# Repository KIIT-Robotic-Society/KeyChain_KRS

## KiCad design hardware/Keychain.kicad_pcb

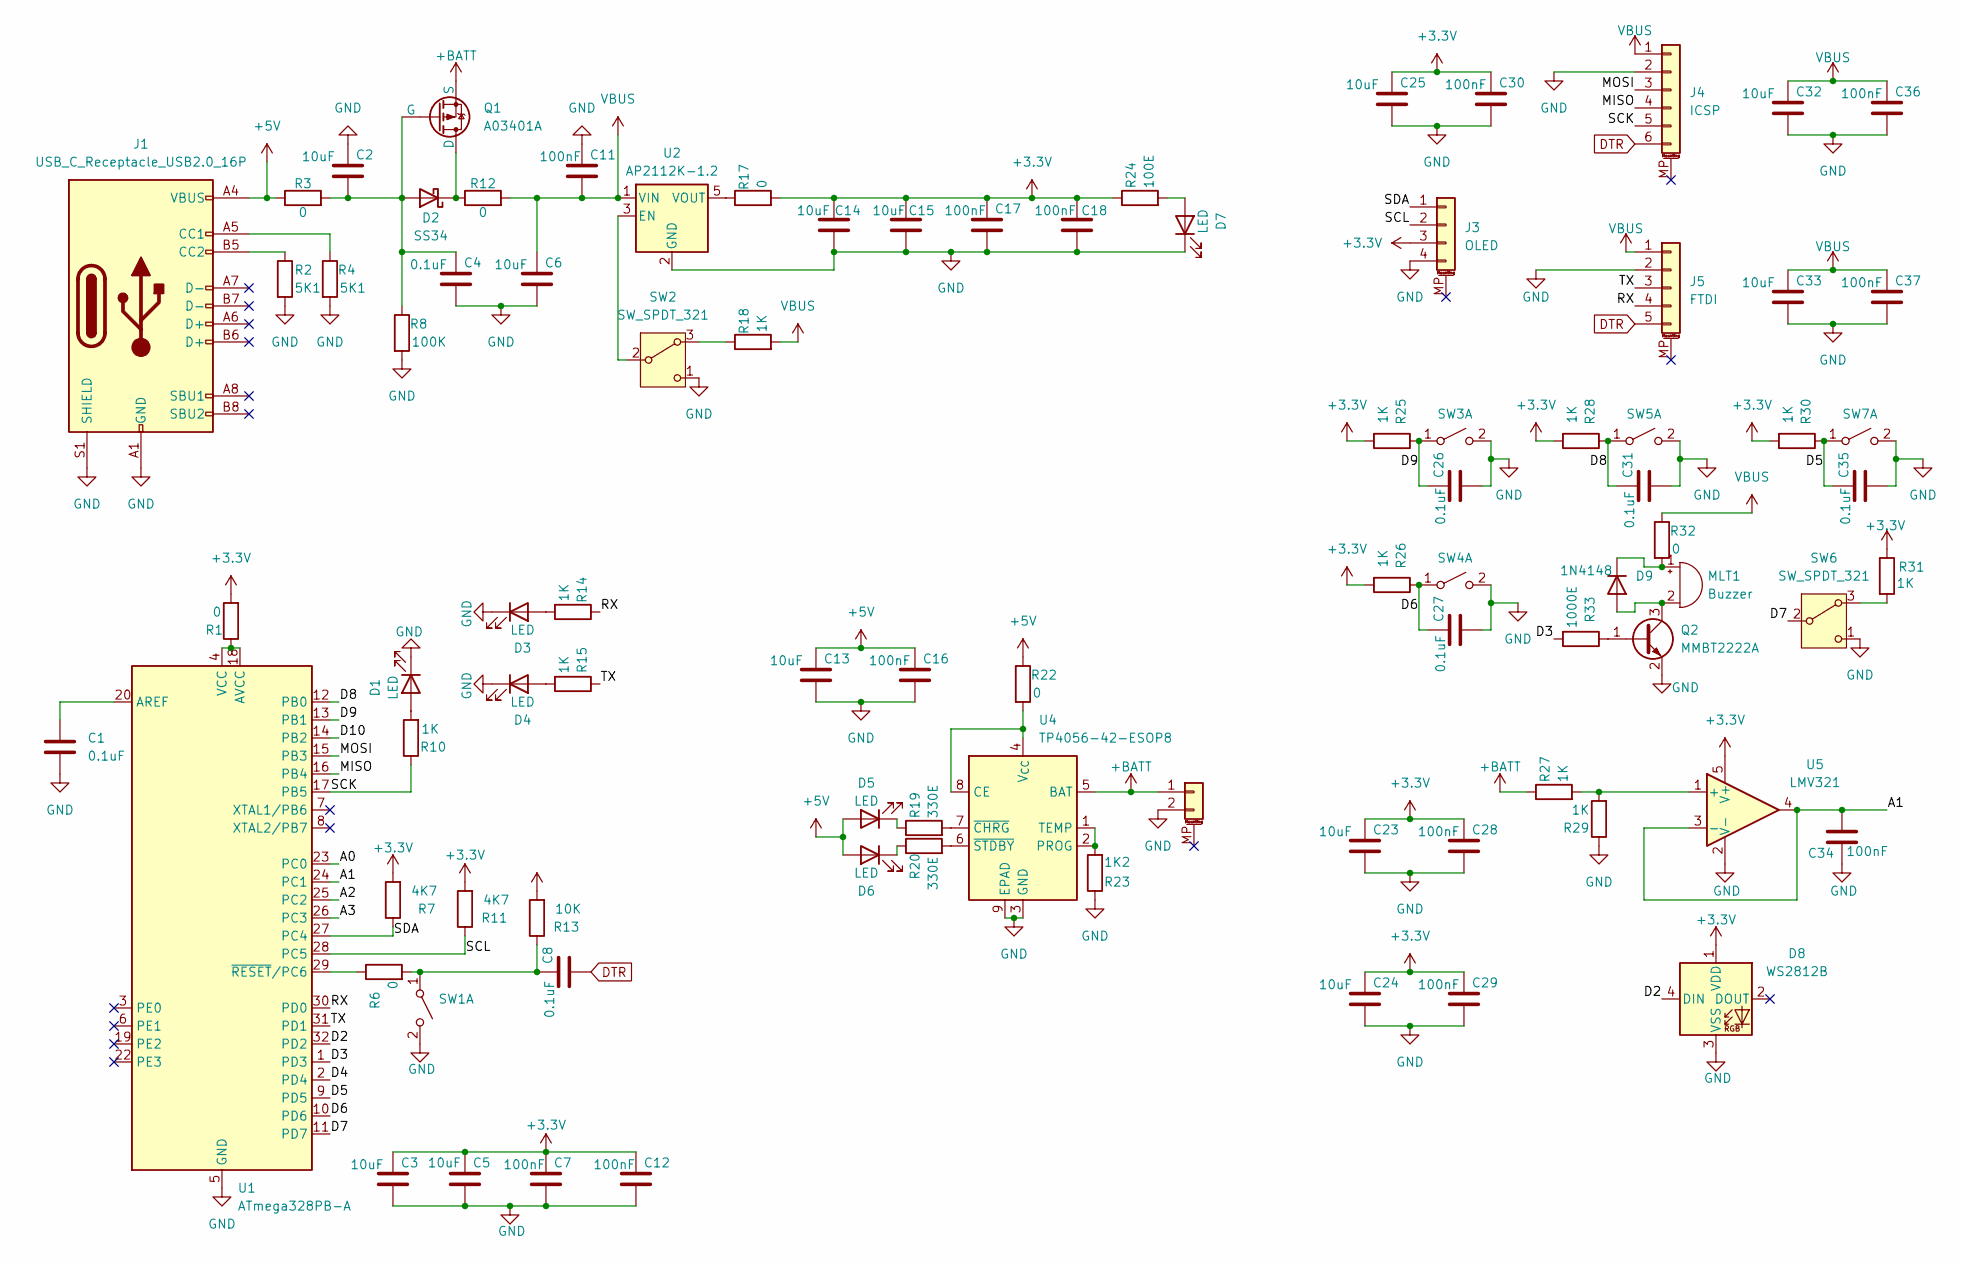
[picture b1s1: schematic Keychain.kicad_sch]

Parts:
C1, C4, C8, C26, C27, C31, C35: 0.1uF; C_0402_1005Metric
C2, C3, C5, C6, C13, C14, C15, C23, C24, C25, C32, C33: 10uF; C_0402_1005Metric
C7, C11, C12, C16, C17, C18, C28, C29, C30, C34, C36, C37: 100nF; C_0402_1005Metric
D1, D3, D4, D5, D6, D7: LED; LED_0402_1005Metric
D2: SS34; D_SMA
D8: WS2812B; LED_WS2812B_PLCC4_5.0x5.0mm_P3.2mm
D9: 1N4148; D_MiniMELF
J1: USB_C_Receptacle_USB2.0_16P; USB_C_Receptacle_GCT_USB4105-xx-A_16P_TopMnt_Horizontal
J2: Conn_01x02_MountingPin; JST_PH_B2B-PH-K_1x02_P2.00mm_Vertical
J3: OLED; PinHeader_1x04_P2.54mm_Vertical
J4: ICSP; JST_GH_BM06B-GHS-TBT_1x06-1MP_P1.25mm_Vertical
J5: FTDI; JST_GH_BM05B-GHS-TBT_1x05-1MP_P1.25mm_Vertical
MLT1: Buzzer; MagneticBuzzer_CUI_CMT-8504-100-SMT
Q1: A03401A; SOT-23
Q2: MMBT2222A; SOT-23
R1, R3, R6, R12, R17, R22, R32: 0; R_0402_1005Metric
R2, R4: 5K1; R_0402_1005Metric
R7, R11: 4K7; R_0402_1005Metric
R8: 100K; R_0402_1005Metric
R10, R14, R15, R18, R25, R26, R27, R28, R29, R30, R31: 1K; R_0402_1005Metric
R13: 10K; R_0402_1005Metric
R19, R20: 330E; R_0402_1005Metric
R23: 1K2; R_0402_1005Metric
R24: 100E; R_0402_1005Metric
R33: 1000E; R_0402_1005Metric
SW1, SW3, SW4, SW5, SW7: SW_DPST_x2; SW_SPST_B3U-1000P-B
SW2, SW6: SW_SPDT_321; SLW-883935_CUD
U1: ATmega328PB-A; TQFP-32_7x7mm_P0.8mm
U2: AP2112K-1.2; SOT-23-5
U4: TP4056-42-ESOP8; SOIC-8-1EP_3.9x4.9mm_P1.27mm_EP2.41x3.3mm_ThermalVias
U5: LMV321; SOT-353_SC-70-5

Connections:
+3.3V: C3.1, C5.1, C7.1, C12.1, C14.1, C15.1, C17.1, C18.1, C23.1, C24.1, C25.1, C28.1, C29.1, C30.1, D8.1 (VDD), J3.3, R1.2, R7.2, R11.2, R13.2, R17.2, R24.1, R25.2, R26.2, R28.2, R30.2, R31.1, U5.5 (V+); also elsewhere on the board
+5V: C13.1, C16.1, D5.2 (A), D6.2 (A), J1.A4 (VBUS), J1.A9 (VBUS), J1.B4 (VBUS), J1.B9 (VBUS), R3.1, R22.1
+BATT: J2.1, Q1.2 (S), R27.1, U4.5 (BAT)
/A0: U1.23 (PC0)
/A1: C34.2, U1.24 (PC1), U5.3 (-), U5.4
/A2: U1.25 (PC2)
/A3: U1.26 (PC3)
/D2: D8.4 (DIN), U1.32 (PD2)
/D3: R33.2, U1.1 (PD3)
/D4: U1.2 (PD4)
/D5: C35.1, R30.1, SW7.1 (A), U1.9 (PD5)
/D6: C27.1, R26.1, SW4.1 (A), U1.10 (PD6)
/D7: SW6.2 (B), U1.11 (PD7)
/D8: C31.1, R28.1, SW5.1 (A), U1.12 (PB0)
/D9: C26.1, R25.1, SW3.1 (A), U1.13 (PB1)
/D10: U1.14 (PB2)
/MISO: J4.4, U1.16 (PB4)
/MOSI: J4.3, U1.15 (PB3)
/RX: J5.4, R14.1, U1.30 (PD0)
/SCK: J4.5, R10.1, U1.17 (PB5)
/SCL: J3.2, R11.1, U1.28 (PC5); also elsewhere on the board
/SDA: J3.1, R7.1, U1.27 (PC4); also elsewhere on the board
/TX: J5.3, R15.1, U1.31 (PD1)
GND: C1.2, C2.1, C3.2, C4.2, C5.2, C6.2, C7.2, C11.1, C12.2, C13.2, C14.2, C15.2, C16.2, C17.2, C18.2, C23.2, C24.2, C25.2, C26.2, C27.2, C28.2, C29.2, C30.2, C31.2, C32.2, C33.2, C34.1, C35.2, C36.2, C37.2, D1.1 (K), D3.1 (K), D4.1 (K), D7.1 (K), D8.3 (VSS), J1.A1 (GND), J1.A12 (GND), J1.B1 (GND), J1.B12 (GND), J1.S1 (SHIELD), J2.2, J3.4, J4.2, J5.2, Q2.2 (E), R2.2, R4.2, R8.2, R23.1, R29.1, SW1.2 (B), SW2.1 (C), SW3.2 (B), SW4.2 (B), SW5.2 (B), SW6.1 (C), SW7.2 (B), U1.5 (GND), U1.21 (GND), U2.2 (GND), U4.3 (GND), U4.9 (EPAD), U5.2 (V-); also elsewhere on the board
unnamed: D1.2 (A), R10.2
unnamed: C2.2, C4.1, D2.2 (A), Q1.1 (G), R3.2, R8.1
unnamed: D2.1 (K), Q1.3 (D), R12.1
unnamed: D3.2 (A), R14.2
unnamed: D4.2 (A), R15.2
unnamed: D5.1 (K), R19.1
unnamed: D6.1 (K), R20.1
unnamed: D7.2 (A), R24.2
unnamed: D9.2 (A), MLT1.2 (-), Q2.3 (C)
unnamed: D9.1 (K), MLT1.1 (+), R32.2
unnamed: J1.A5 (CC1), R4.1
unnamed: J1.B5 (CC2), R2.1
unnamed: Q2.1 (B), R33.1
unnamed: C8.1, R6.2, R13.1, SW1.1 (A)
unnamed: R18.1, SW2.3 (A)
unnamed: SW2.2 (B), U2.3 (EN)
unnamed: R31.2, SW6.3 (A)
unnamed: C1.1, U1.20 (AREF)
unnamed: R1.1, U1.4 (VCC), U1.18 (AVCC)
unnamed: R17.1, U2.5 (VOUT)
unnamed: R22.2, U4.4 (V_{CC}), U4.8 (CE)
unnamed: R23.2, U4.1 (TEMP), U4.2 (PROG)
unnamed: R19.2, U4.7 (~CHRG)
unnamed: R20.2, U4.6 (~STDBY)
unnamed: R27.2, R29.2, U5.1 (+)
VBUS: C6.1, C11.2, C32.1, C33.1, C36.1, C37.1, J4.1, J5.1, R12.2, R18.2, R32.1, U2.1 (VIN); also elsewhere on the board

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
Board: 2 copper layers, 97 parts (30 on the bottom side), 51 nets, no tracks yet.

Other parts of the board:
C19, C38: 10uF; C_0402_1005Metric
C20: 2.2nF; C_0402_1005Metric
C21: 0.1uF; C_0402_1005Metric
C22, C39: 100nF; C_0402_1005Metric
R16: 1K; R_0402_1005Metric
R21: 0; R_0402_1005Metric
U3: MPU-6050; InvenSense_QFN-24_4x4mm_P0.5mm

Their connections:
+3.3V: C19.1, C22.1, R21.1; also elsewhere on the board
/SCL: U3.23 (SCL); also elsewhere on the board
/SDA: U3.24 (SDA); also elsewhere on the board
GND: C19.2, C20.2, C21.2, C22.2, C38.2, C39.2, R16.1, U3.1 (CLKIN), U3.11 (FSYNC), U3.18 (GND); also elsewhere on the board
unnamed: R16.2, U3.9 (AD0)
unnamed: C21.1, U3.20 (CPOUT)
unnamed: C20.1, U3.10 (REGOUT)
unnamed: R21.2, U3.8 (VLOGIC), U3.13 (VDD)
VBUS: C38.1, C39.1; also elsewhere on the board

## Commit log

2025-07-25 chore: add schematic file
